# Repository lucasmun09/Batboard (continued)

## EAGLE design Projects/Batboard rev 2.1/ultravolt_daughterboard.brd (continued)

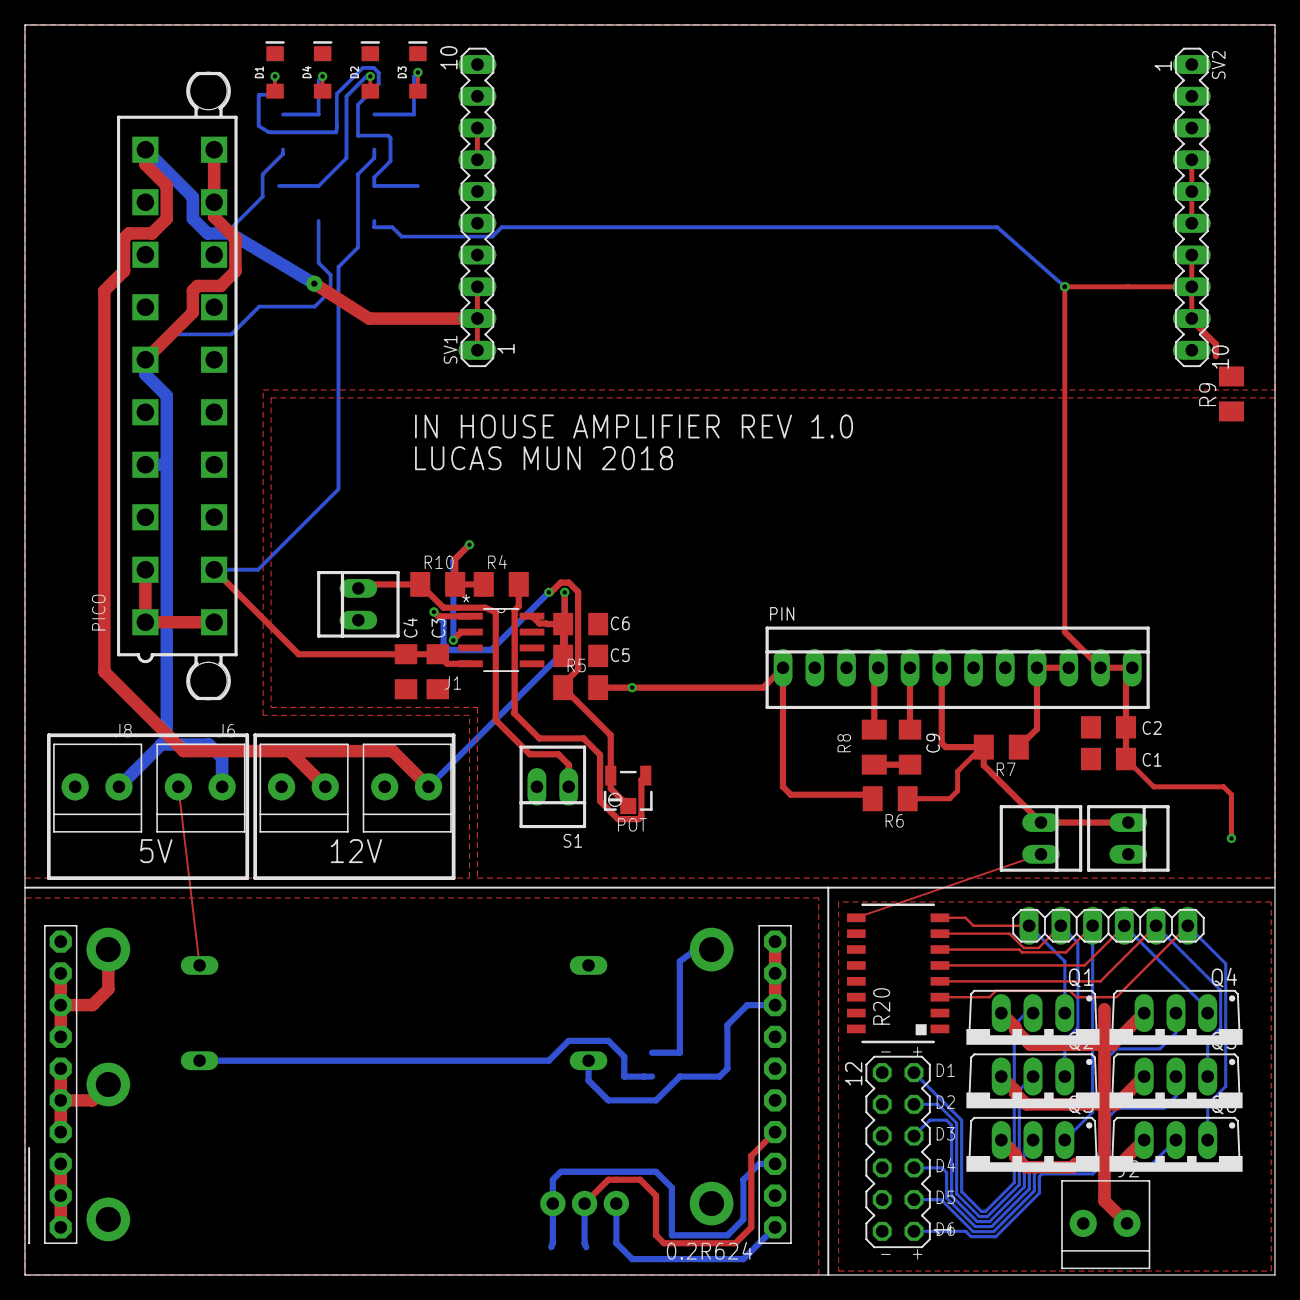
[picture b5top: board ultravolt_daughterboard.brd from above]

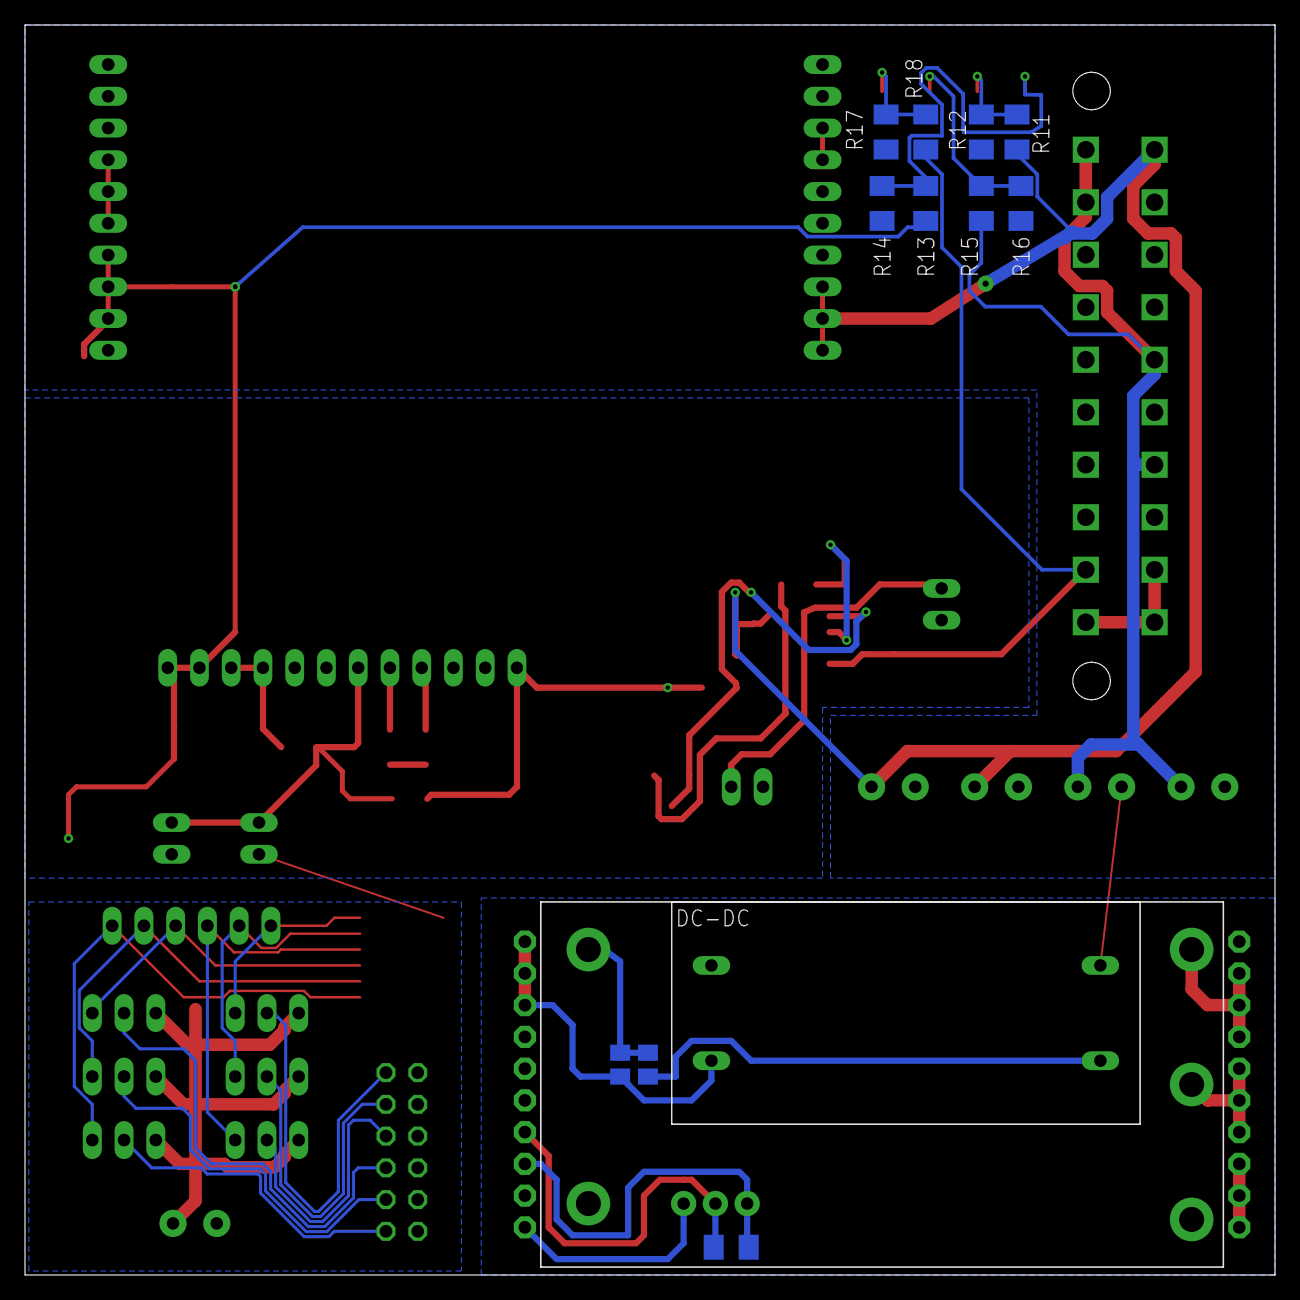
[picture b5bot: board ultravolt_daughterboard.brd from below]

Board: 2 copper layers, 100.0 x 100.0 mm, 57 parts (12 on the bottom side), 42 nets.

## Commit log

2018-06-19 File management
2018-06-22 Checked ERC and DRC
2018-06-25 BOM generation started
2018-06-25 Updated BOM
2018-06-26 Updated capacitors for switching step down regulators
2018-07-02 Not sure
2018-07-02 Updated LEDS
2018-07-03 Fixed back to "Updated LEDs"
2018-08-27 Update with Microphones
2018-10-14 Havent done this in a while
